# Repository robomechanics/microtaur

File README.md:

# microtaur
The design files and code for the microtaur.

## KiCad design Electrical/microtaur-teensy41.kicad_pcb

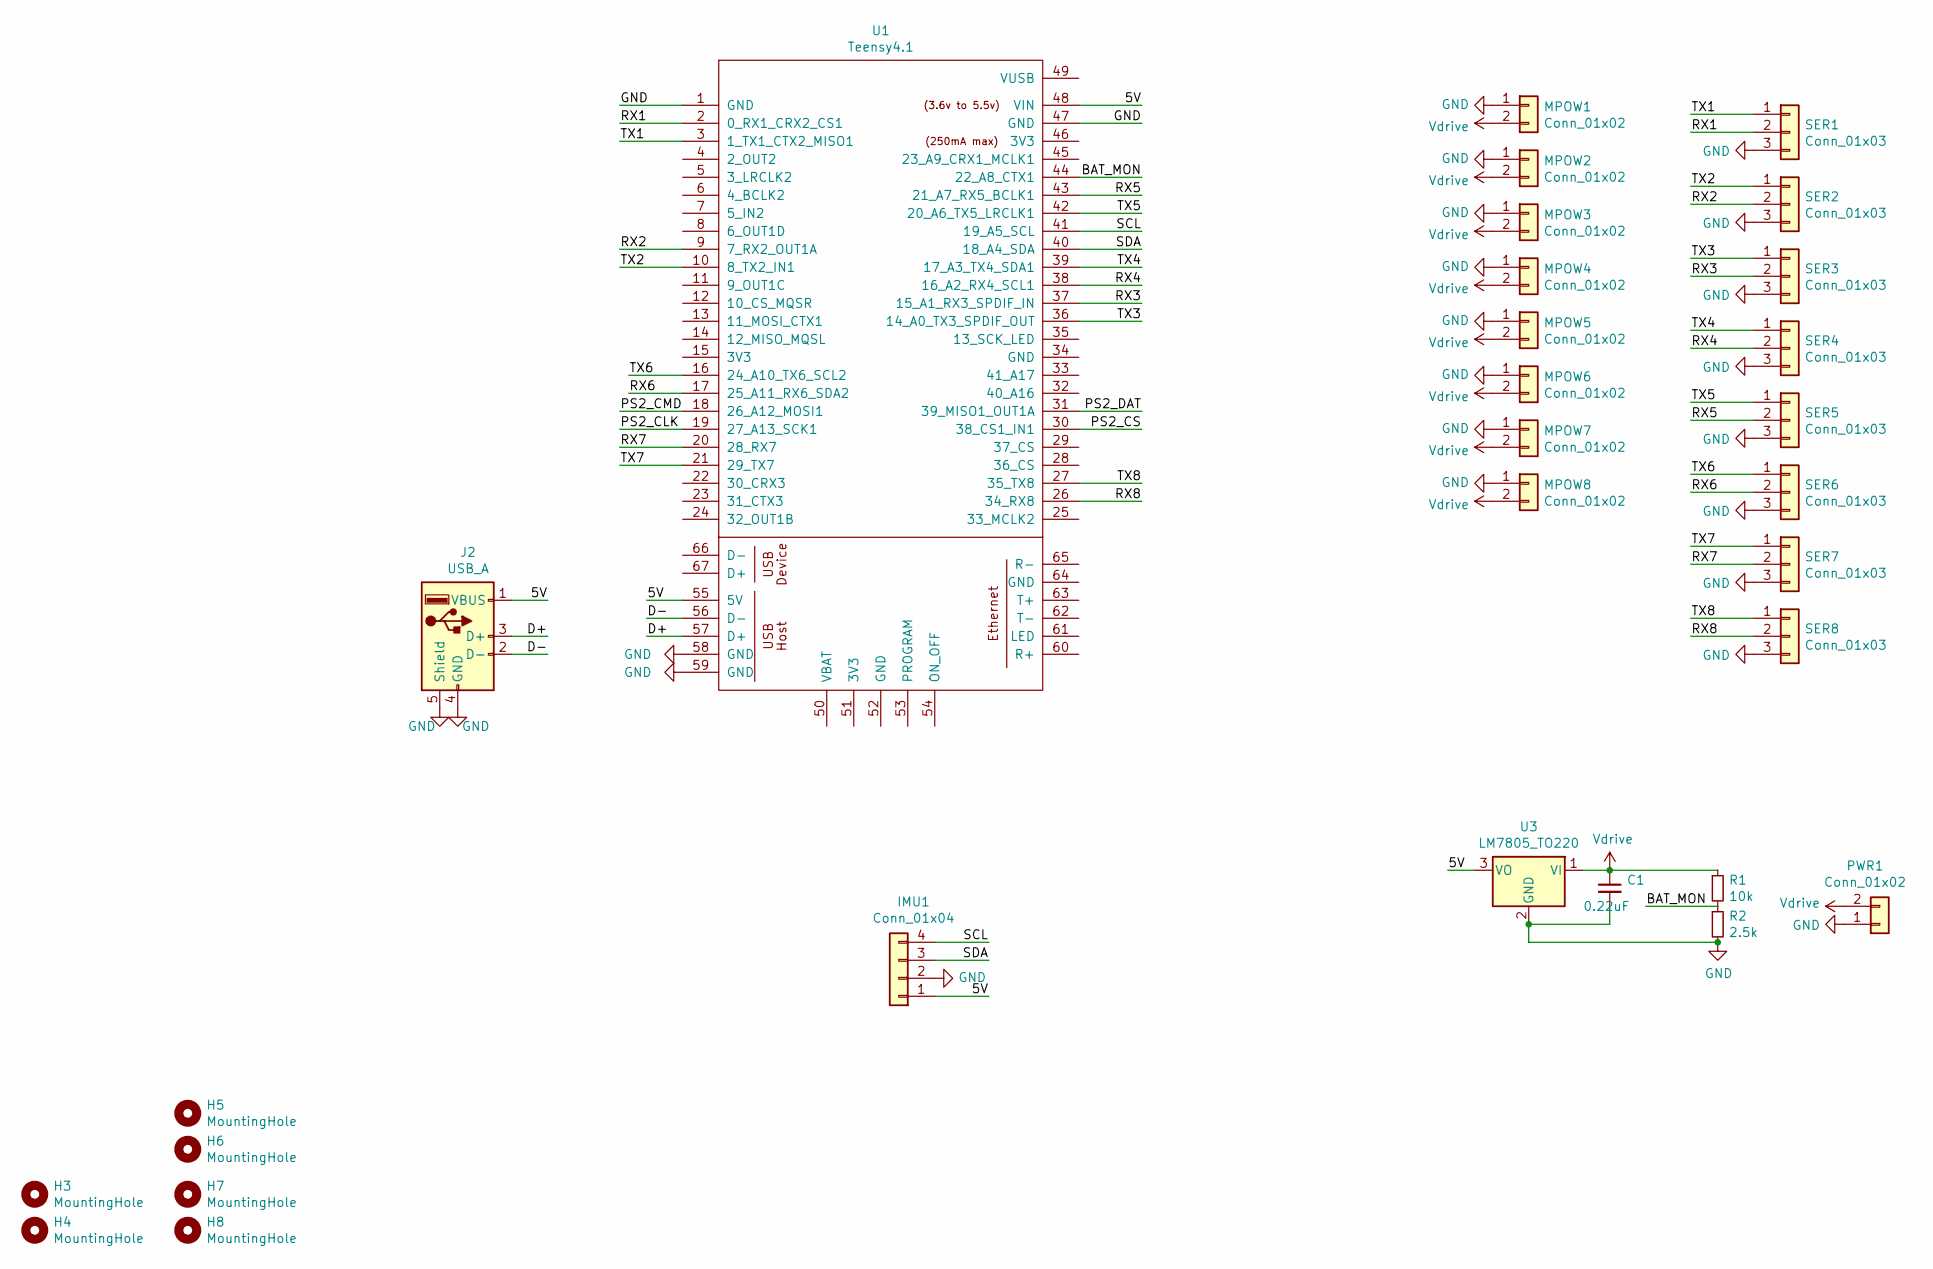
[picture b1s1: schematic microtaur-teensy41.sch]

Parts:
C1: 0.22uF; C_0805_2012Metric_Pad1.15x1.40mm_HandSolder; Part Number 2679-C0805X7R500-22MNETR-ND
H3, H4, H5, H6, H7, H8: MountingHole; MountingHole_2.2mm_M2
IMU1: Conn_01x04; JST_SH_SM04B-SRSS-TB_1x04-1MP_P1.00mm_Horizontal; Part Number 455-1790-2-ND
J2: USB_A; USB_A_Molex_105057_Vertical; Part Number WM8672-ND
MPOW1, MPOW2, MPOW3, MPOW4, MPOW5, MPOW6, MPOW7, MPOW8: Conn_01x02; AMASS_XT30U-F_1x02_P5.0mm_Vertical
PWR1: Conn_01x02; AMASS_XT30U-F_1x02_P5.0mm_Vertical
R1: 10k; R_0603_1608Metric_Pad1.05x0.95mm_HandSolder; Part Number 541-2795-2-ND
R2: 2.5k; R_0603_1608Metric_Pad1.05x0.95mm_HandSolder; Part Number 541-RCS06032K49FKEATR-ND
SER1, SER2, SER3, SER4, SER5, SER6, SER7, SER8: Conn_01x03; JST_SH_SM03B-SRSS-TB_1x03-1MP_P1.00mm_Horizontal; Part Number 455-1803-2-ND
U1: Teensy4.1; Teensy41
U3: LM7805_TO220; SOT-223; Part Number NCP1117LPST33T3COSTR-ND

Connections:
/5V: IMU1.1, J2.1 (VBUS), U1.48 (VIN), U1.55 (5V), U3.3 (VO)
/BAT_MON: R1.2, R2.1, U1.44 (22_A8_CTX1)
/D+: J2.3 (D+), U1.57 (D+)
/D-: J2.2 (D-), U1.56 (D-)
/PS2_CLK: U1.19 (27_A13_SCK1)
/PS2_CMD: U1.18 (26_A12_MOSI1)
/PS2_CS: U1.30 (38_CS1_IN1)
/PS2_DAT: U1.31 (39_MISO1_OUT1A)
/RX1: SER1.2, U1.2 (0_RX1_CRX2_CS1)
/RX2: SER2.2, U1.9 (7_RX2_OUT1A)
/RX3: SER3.2, U1.37 (15_A1_RX3_SPDIF_IN)
/RX4: SER4.2, U1.38 (16_A2_RX4_SCL1)
/RX5: SER5.2, U1.43 (21_A7_RX5_BCLK1)
/RX6: SER6.2, U1.17 (25_A11_RX6_SDA2)
/RX7: SER7.2, U1.20 (28_RX7)
/RX8: SER8.2, U1.26 (34_RX8)
/SCL: IMU1.4, U1.41 (19_A5_SCL)
/SDA: IMU1.3, U1.40 (18_A4_SDA)
/TX1: SER1.1, U1.3 (1_TX1_CTX2_MISO1)
/TX2: SER2.1, U1.10 (8_TX2_IN1)
/TX3: SER3.1, U1.36 (14_A0_TX3_SPDIF_OUT)
/TX4: SER4.1, U1.39 (17_A3_TX4_SDA1)
/TX5: SER5.1, U1.42 (20_A6_TX5_LRCLK1)
/TX6: SER6.1, U1.16 (24_A10_TX6_SCL2)
/TX7: SER7.1, U1.21 (29_TX7)
/TX8: SER8.1, U1.27 (35_TX8)
GND: C1.2, IMU1.2, J2.4 (GND), J2.5 (Shield), MPOW1.1, MPOW2.1, MPOW3.1, MPOW4.1, MPOW5.1, MPOW6.1, MPOW7.1, MPOW8.1, PWR1.1, R2.2, SER1.3, SER2.3, SER3.3, SER4.3, SER5.3, SER6.3, SER7.3, SER8.3, U1.1 (GND), U1.47 (GND), U1.58 (GND), U1.59 (GND), U3.2 (GND)
Vdrive: C1.1, MPOW1.2, MPOW2.2, MPOW3.2, MPOW4.2, MPOW5.2, MPOW6.2, MPOW7.2, MPOW8.2, PWR1.2, R1.1, U3.1 (VI)

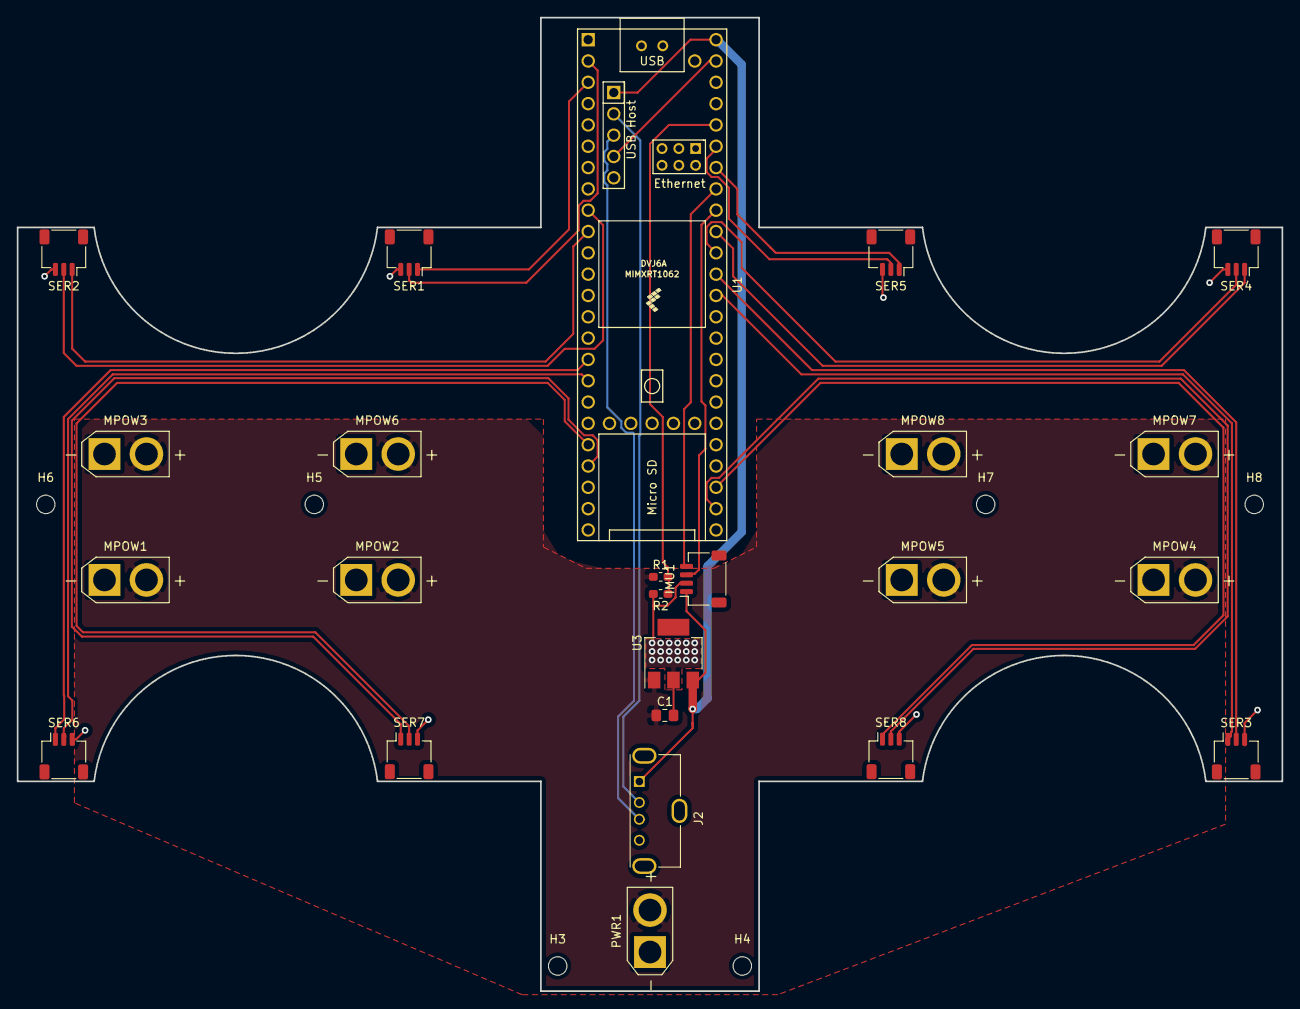
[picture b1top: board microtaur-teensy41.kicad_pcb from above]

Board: 2 copper layers, 150.7 x 116.0 mm, 30 parts (0 on the bottom side), 24 nets.

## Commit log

2021-07-02 Added kicad files
2021-07-02 added gitignore for pcb
2021-07-02 applied gitignore
2021-07-02 added .gitattributes file
2021-07-02 Added mechanical design files
2021-07-02 added firmware
2021-08-13 added package3d in pcb
2021-08-13 updated solidworks model
2021-09-27 Updated pcb to check compatibility with mcad
2021-09-27 completed pcb design, ready to fab
2021-10-20 Joystick Working with RTOS
2021-10-21 led status indication working
2021-10-22 Added the controller state machine.
2021-10-24 Added updates to the cad model
2021-10-29 update joy callback name
2021-11-02 added missing mechanical subassemblies
2021-11-05 add firmware readme
2021-11-05 added documentation to the machine class.
2021-11-05 added a multi-threaded iq serial class
2021-11-05 switched the set function to handle only millisecond integers
2021-11-05 improved sleep in machine, switched from a map to an unordered map to store controllers.
2021-11-05 moved imu sleep to the main thread
2021-11-05 updated motor class to use the multi-threaded iq serial libr
2021-11-07 Tested motor thread with 2 motors. Working at 200Hz.
2021-11-10 updated the iq motion control library to the forked version on the robomechanics github account.
2022-02-14 Comms test
2022-06-13 Update main.cpp
    First stand
2022-07-20 Update microtaur.h
    Can:
    Bound, (const. speed)
    Walk-trot-fwd (const. speed)
    Walk-trot-bckwd (const. speed)
    Hop
    Enter a spider-like stance (revert)
2023-05-04 Update Microtaur Implementation
    Mainly modified Microtaur.h and main.cpp to implement behavior functions. Implemented trot, hop, bound, etc. and data collection features
2023-05-04 Modified leg links to minimize number of bearings
2023-05-04 Microtaur behavior trials (Voltage Recordings)
2023-05-04 Instructions to update/debug VERTIQ 220kv 23-06
2023-12-15 Adding altered code with turning gaits
    from spine project
2024-10-01 Add pio dependencies and cleaned up microtaur.h
    With this commit, the lib dependencies for this project are added such that on pull, developers can open this as an existing project via the PIO UI. In this commit, microtaur.h is cleaned of dead cod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
